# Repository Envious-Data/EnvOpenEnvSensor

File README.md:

# EnvOpenEnvSensor
 a simple sensor pcb with a display to show some environment conditions

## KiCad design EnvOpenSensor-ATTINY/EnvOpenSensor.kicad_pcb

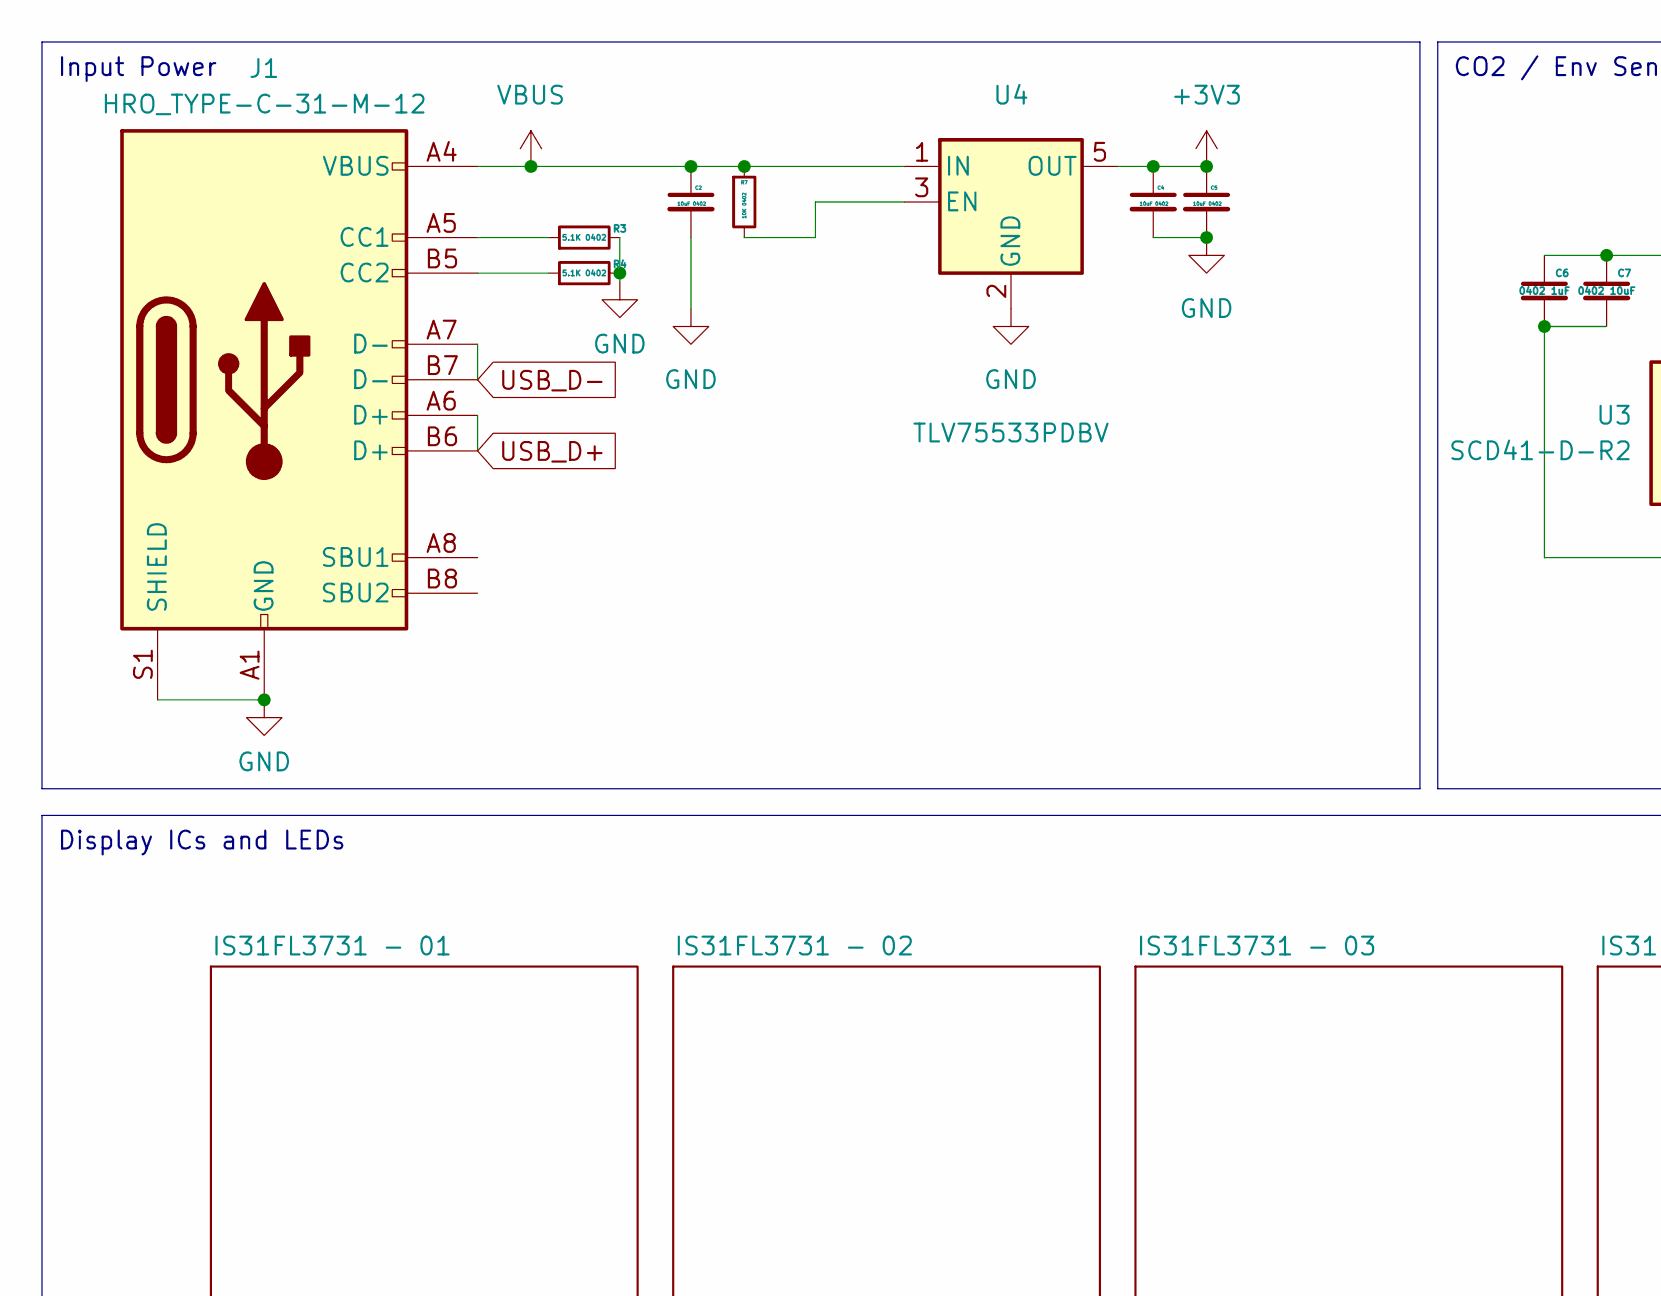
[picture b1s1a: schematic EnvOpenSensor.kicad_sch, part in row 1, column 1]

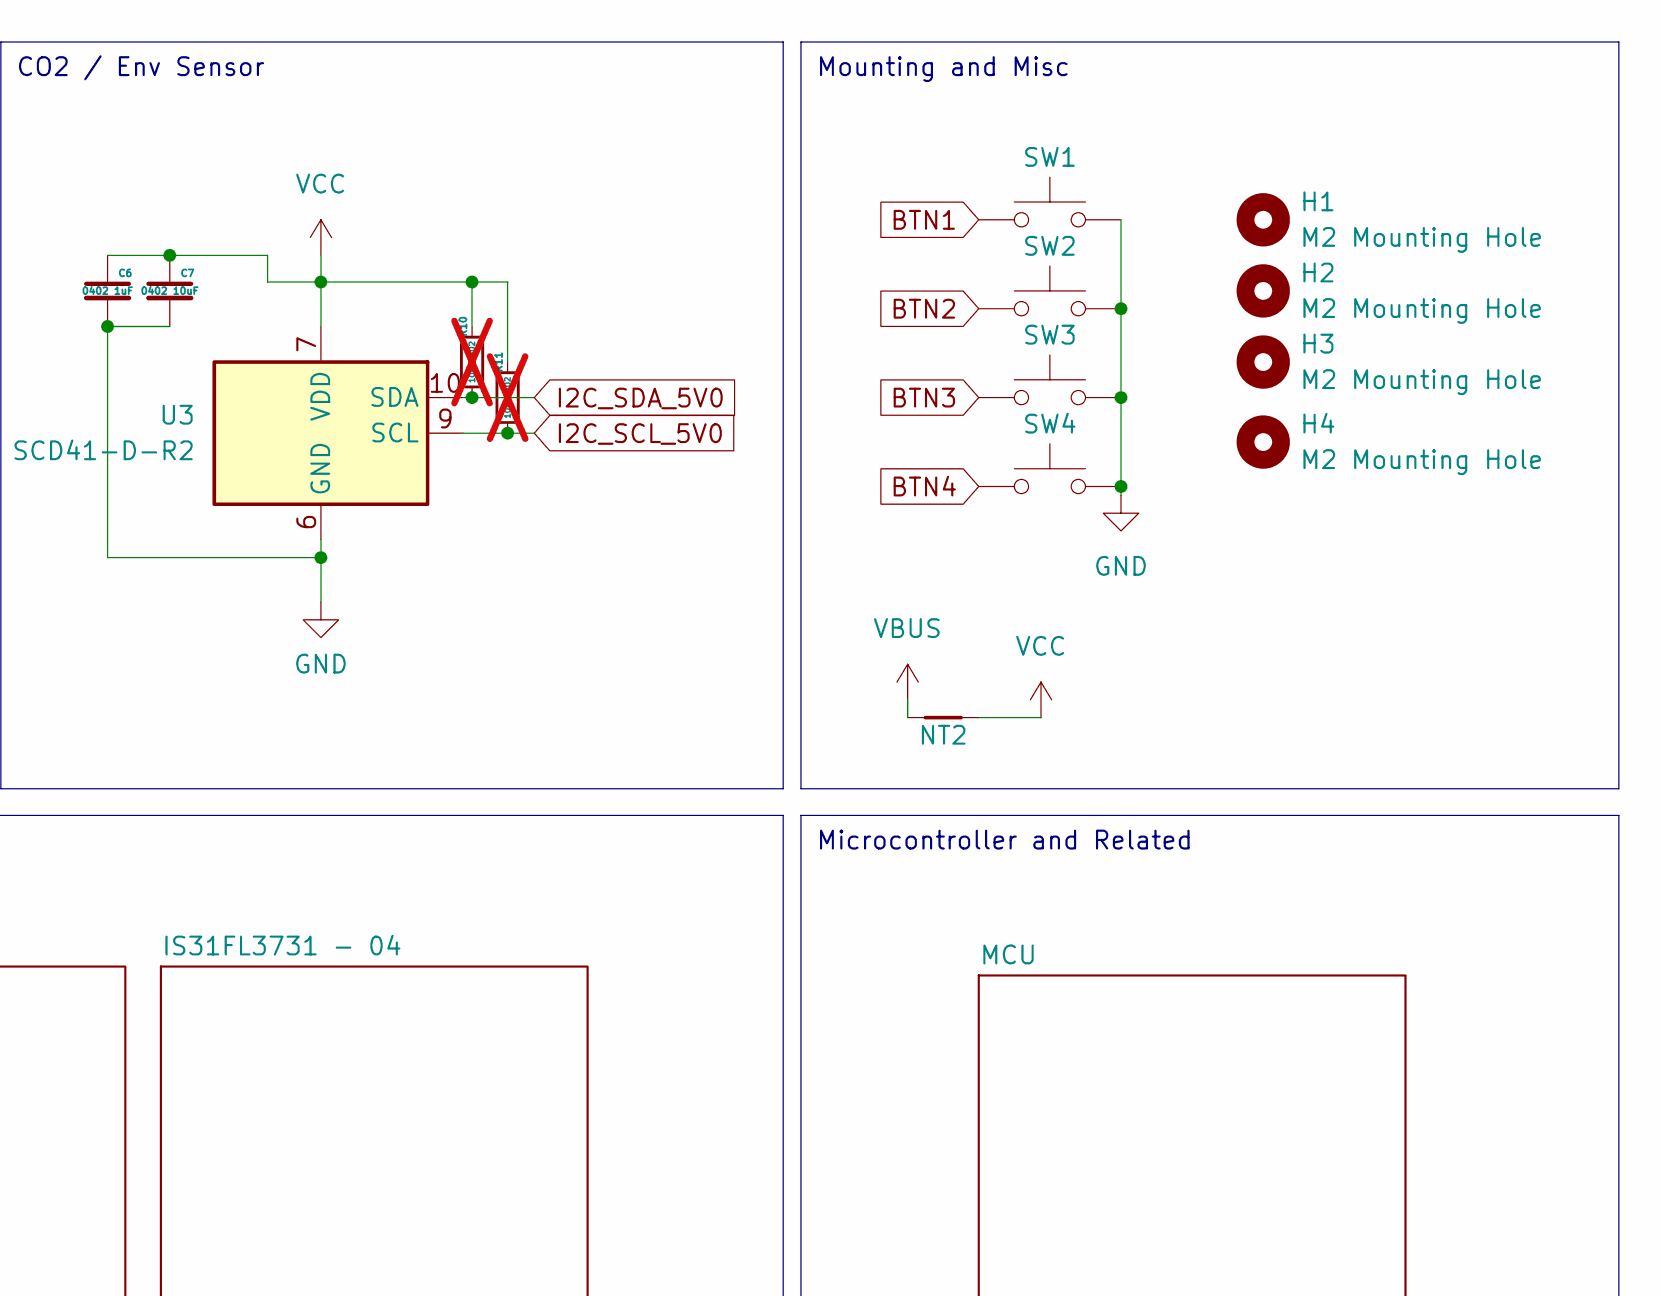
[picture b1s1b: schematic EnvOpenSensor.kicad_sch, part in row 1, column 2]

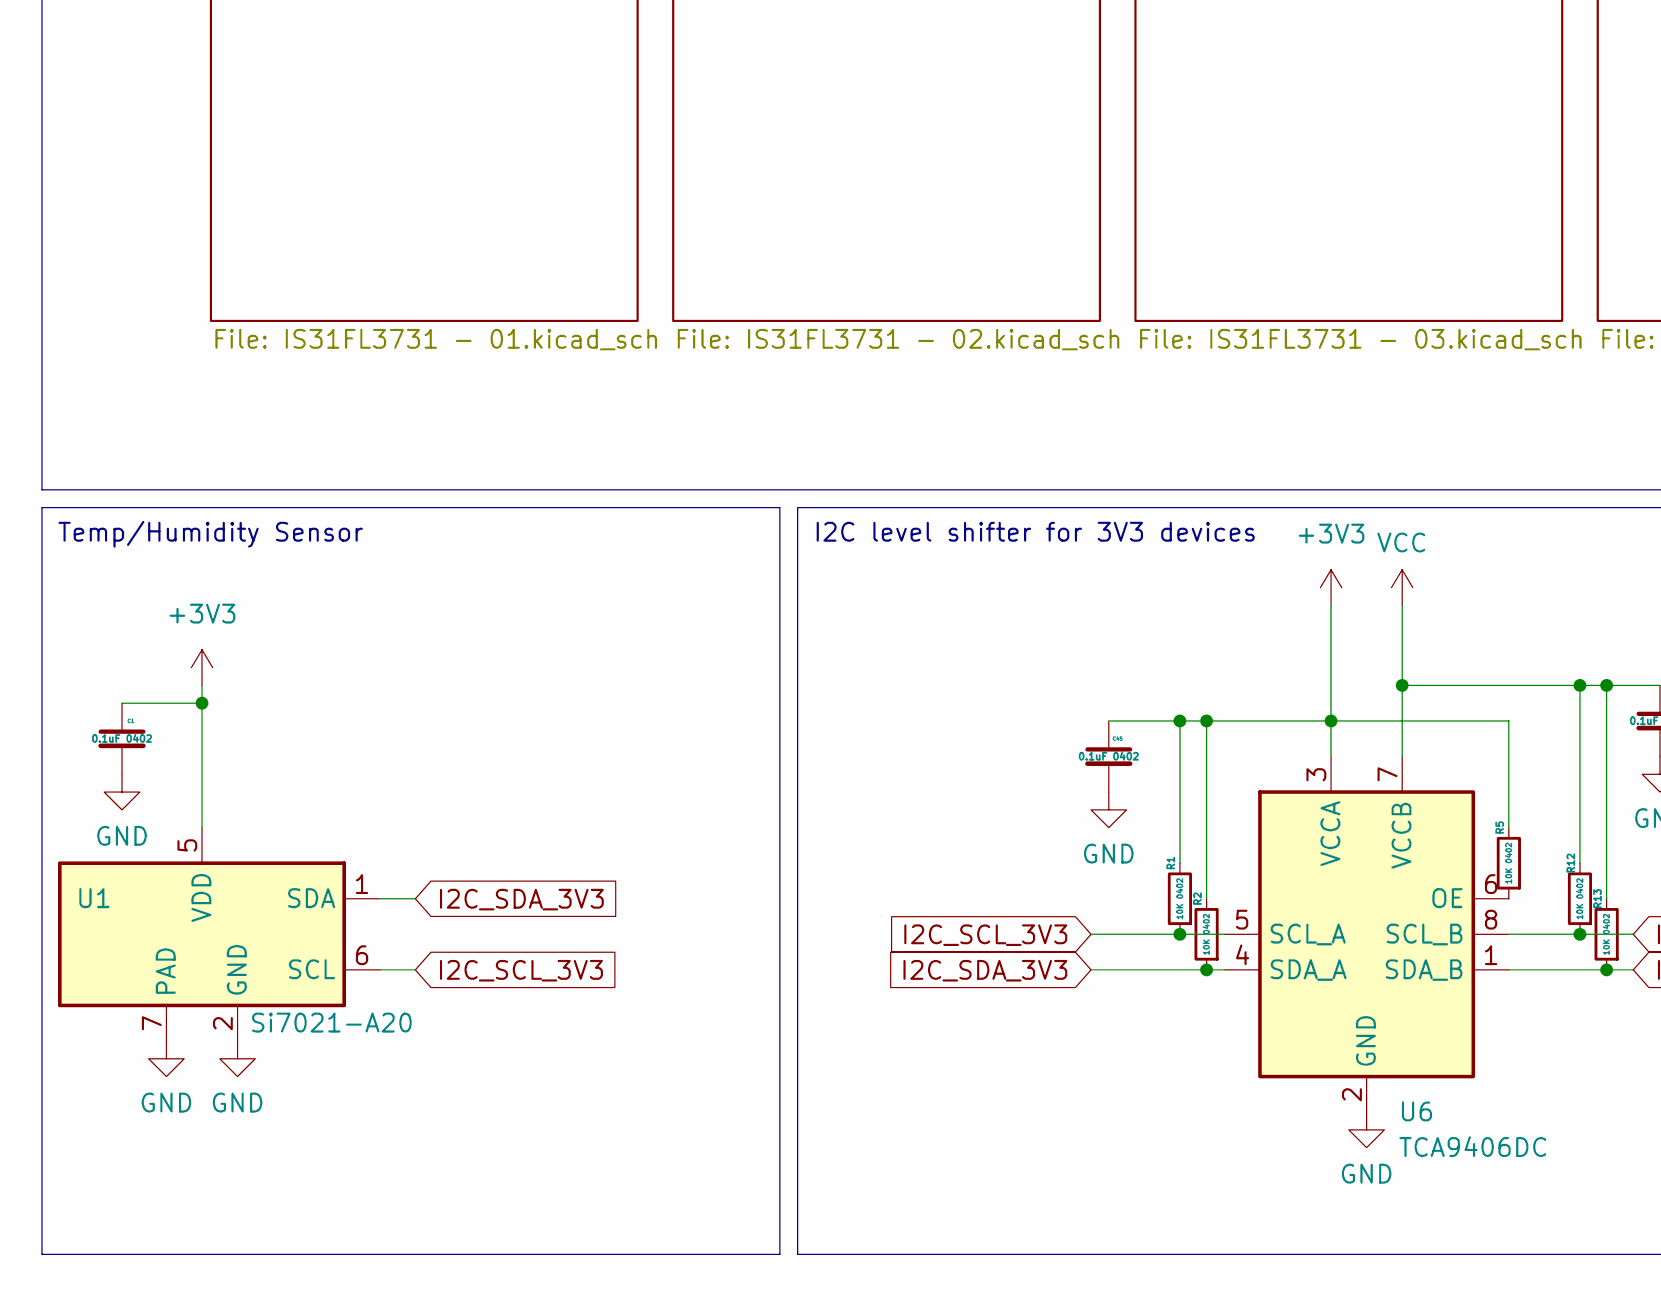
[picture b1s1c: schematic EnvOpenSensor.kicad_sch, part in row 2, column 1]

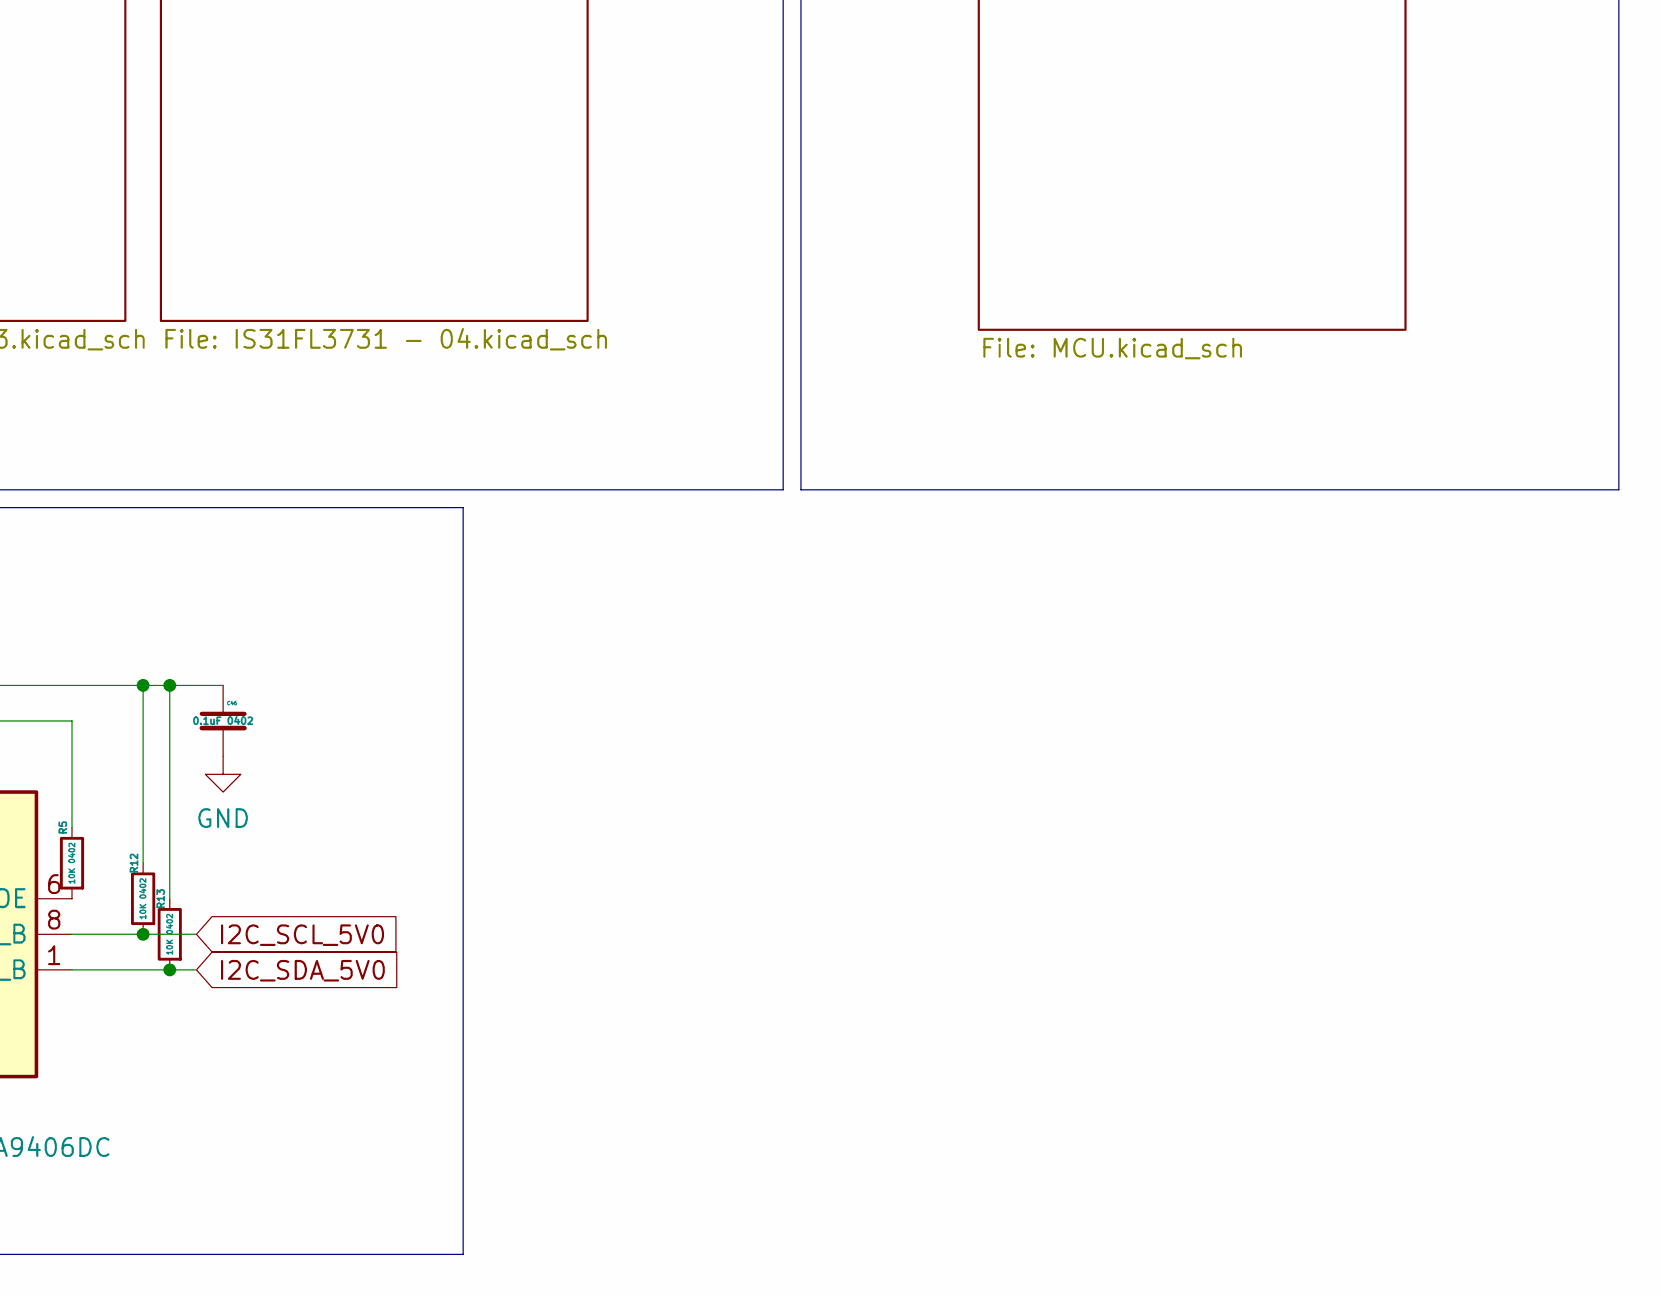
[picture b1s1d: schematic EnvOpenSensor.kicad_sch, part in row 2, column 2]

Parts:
C1, C45, C46: 0.1uF 0402; C_0402_1005Metric
C2, C4, C5: 10uF 0402; C_0402_1005Metric
C6: 0402 1uF; C_0402_1005Metric
C7: 0402 10uF; C_0402_1005Metric
H1, H2, H3, H4: M2 Mounting Hole; MountingHole_2.2mm_M2
J1: HRO_TYPE-C-31-M-12; USB_C_Receptacle_HRO_TYPE-C-31-M-12
NT2: NetTie_2; NetTie-2_THT_Pad1.0mm
R1, R2, R5, R7, R12, R13: 10K 0402; R_0402_1005Metric
R3, R4: 5.1K 0402; R_0402_1005Metric
R10, R11: 10K 0402; R_0402_1005Metric; not fitted
SW1, SW2, SW3, SW4: SW_Push; SW_Cherry_MX_1.00u_PCB
U1: Si7021-A20; DFN-6-1EP_3x3mm_P1mm_EP1.5x2.4mm
U3: SCD41-D-R2; Sensirion_SCD4x-1EP_10.1x10.1mm_P1.25mm_EP4.8x4.8mm
U4: TLV75533PDBV; SOT-23-5
U6: TCA9406DC; VSSOP-8_2.3x2mm_P0.5mm

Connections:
+3V3: C1.1, C4.1, C5.1, C45.1, R1.2, R2.2, R5.2, U1.5 (VDD), U4.5 (OUT), U6.3 (VCCA); also elsewhere on the board
BTN1: SW1.1; also elsewhere on the board
BTN2: SW2.1; also elsewhere on the board
BTN3: SW3.1; also elsewhere on the board
BTN4: SW4.1; also elsewhere on the board
GND: C1.2, C2.2, C4.2, C5.2, C6.2, C7.2, C45.2, C46.2, J1.A1 (GND), J1.A12 (GND), J1.B1 (GND), J1.B12 (GND), J1.S1 (SHIELD), R3.2, R4.2, SW1.2, SW2.2, SW3.2, SW4.2, U1.2 (GND), U1.7 (PAD), U3.6 (GND), U3.20 (GND), U3.21 (GND), U4.2 (GND), U6.2 (GND); also elsewhere on the board
I2C_SCL_3V3: R1.1, U1.6 (SCL), U6.5 (SCL_A); also elsewhere on the board
I2C_SCL_5V0: R11.1, R12.1, U3.9 (SCL), U6.8 (SCL_B); also elsewhere on the board
I2C_SDA_3V3: R2.1, U1.1 (SDA), U6.4 (SDA_A); also elsewhere on the board
I2C_SDA_5V0: R10.1, R13.1, U3.10 (SDA), U6.1 (SDA_B); also elsewhere on the board
unnamed: J1.A5 (CC1), R3.1
unnamed: J1.B5 (CC2), R4.1
unnamed: R7.2, U4.3 (EN)
unnamed: R5.1, U6.6 (OE)
USB_D+: J1.A6 (D+), J1.B6 (D+)
USB_D-: J1.A7 (D-), J1.B7 (D-)
VBUS: C2.1, J1.A4 (VBUS), J1.A9 (VBUS), J1.B4 (VBUS), J1.B9 (VBUS), NT2.1, R7.1, U4.1 (IN)
VCC: C6.1, C7.1, C46.1, NT2.2, R10.2, R11.2, R12.2, R13.2, U3.7 (VDD), U3.19 (VDD), U6.7 (VCCB); also elsewhere on the board

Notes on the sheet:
CO2 / Env Sensor
Temp/Humidity Sensor
Mounting and Misc
I2C level shifter for 3V3 devices
Input Power
Microcontroller and Related
Display ICs and LEDs

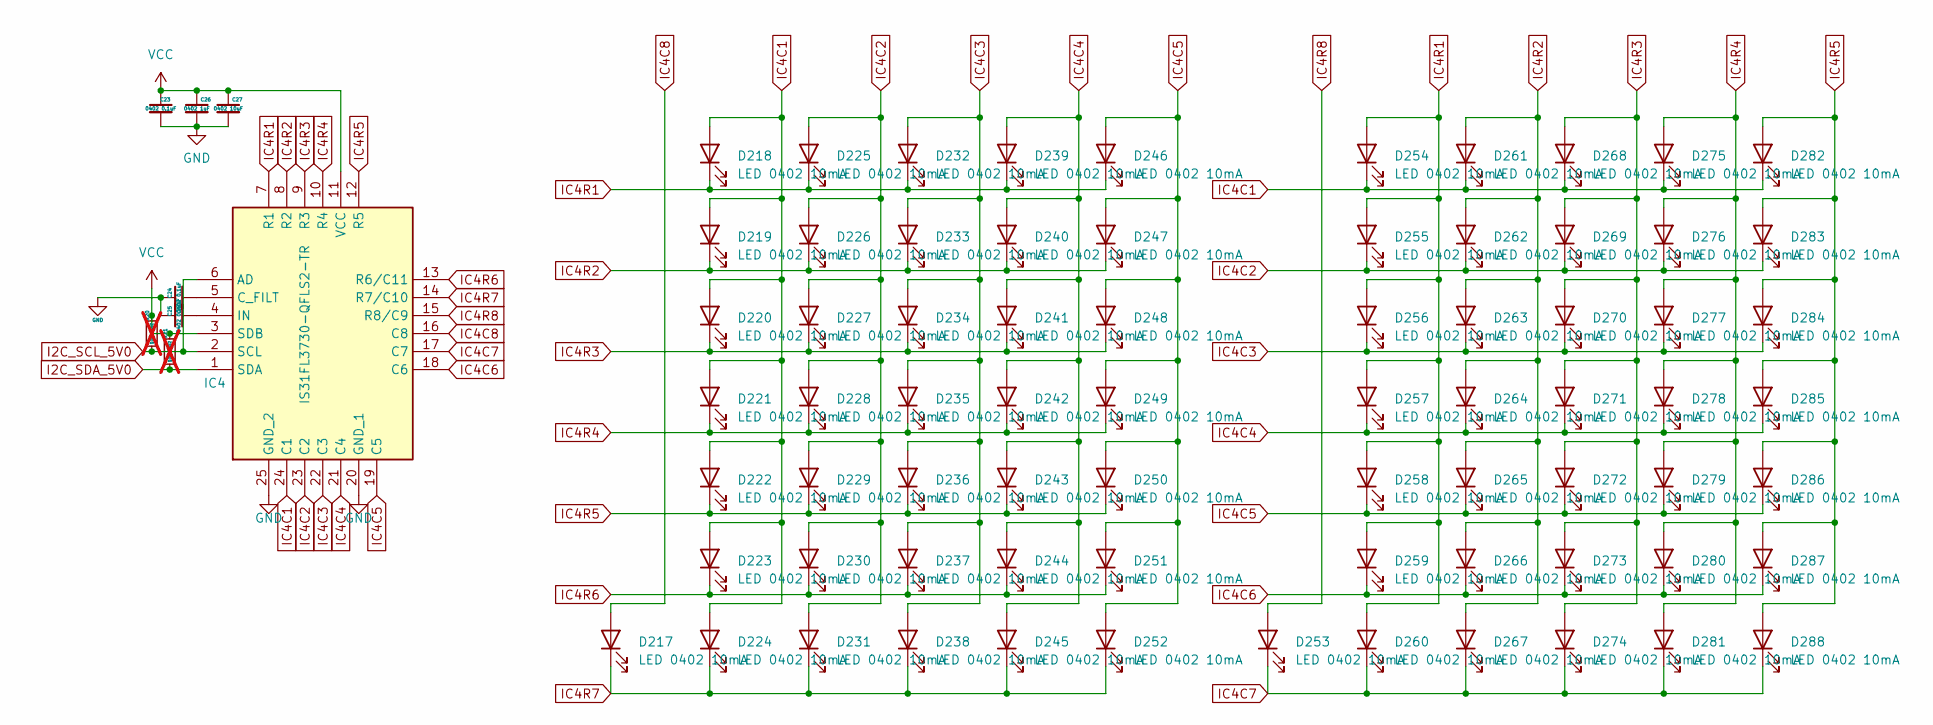
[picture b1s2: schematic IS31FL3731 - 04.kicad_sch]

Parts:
C23, C24: 0402 0.1uF; C_0402_1005Metric
C25: 0402 0.22uF; C_0402_1005Metric
C26: 0402 1uF; C_0402_1005Metric
C27: 0402 10uF; C_0402_1005Metric
D217, D218, D219, D220, D221, D222, D223, D224, D225, D226, D227, D228, D229, D230, D231, D232, D233, D234, D235, D236, D237, D238, D239, D240, D241, D242, D243, D244, D245, D246, D247, D248, D249, D250, D251, D252, D253, D254, D255, D256, D257, D258, D259, D260, D261, D262, D263, D264, D265, D266, D267, D268, D269, D270, D271, D272, D273, D274, D275, D276, D277, D278, D279, D280, D281, D282, D283, D284, D285, D286, D287, D288: LED 0402 10mA; LED_0402_1005Metric
IC4: IS31FL3730-QFLS2-TR; QFN-24-1EP_4x4mm_P0.5mm_EP2.6x2.6mm_ThermalVias; Mouser Part Number 870-IS31FL3730QFLS2R
R20, R21: 10K 0402; R_0402_1005Metric; not fitted

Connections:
GND: C23.2, C24.1, C25.1, C26.2, C27.2, IC4.20 (GND_1), IC4.25 (GND_2); also elsewhere on the board
I2C_SCL_5V0: IC4.2 (SCL), IC4.6 (AD), R20.1; also elsewhere on the board
I2C_SDA_5V0: IC4.1 (SDA), R21.1; also elsewhere on the board
IC4C1: D218.2 (A), D219.2 (A), D220.2 (A), D221.2 (A), D222.2 (A), D223.2 (A), D224.2 (A), D254.1 (K), D261.1 (K), D268.1 (K), D275.1 (K), D282.1 (K), IC4.24 (C1)
IC4C2: D225.2 (A), D226.2 (A), D227.2 (A), D228.2 (A), D229.2 (A), D230.2 (A), D231.2 (A), D255.1 (K), D262.1 (K), D269.1 (K), D276.1 (K), D283.1 (K), IC4.23 (C2)
IC4C3: D232.2 (A), D233.2 (A), D234.2 (A), D235.2 (A), D236.2 (A), D237.2 (A), D238.2 (A), D256.1 (K), D263.1 (K), D270.1 (K), D277.1 (K), D284.1 (K), IC4.22 (C3)
IC4C4: D239.2 (A), D240.2 (A), D241.2 (A), D242.2 (A), D243.2 (A), D244.2 (A), D245.2 (A), D257.1 (K), D264.1 (K), D271.1 (K), D278.1 (K), D285.1 (K), IC4.21 (C4)
IC4C5: D246.2 (A), D247.2 (A), D248.2 (A), D249.2 (A), D250.2 (A), D251.2 (A), D252.2 (A), D258.1 (K), D265.1 (K), D272.1 (K), D279.1 (K), D286.1 (K), IC4.19 (C5)
IC4C6: D259.1 (K), D266.1 (K), D273.1 (K), D280.1 (K), D287.1 (K), IC4.18 (C6)
IC4C7: D253.1 (K), D260.1 (K), D267.1 (K), D274.1 (K), D281.1 (K), D288.1 (K), IC4.17 (C7)
IC4C8: D217.2 (A), IC4.16 (C8)
IC4R1: D218.1 (K), D225.1 (K), D232.1 (K), D239.1 (K), D246.1 (K), D254.2 (A), D255.2 (A), D256.2 (A), D257.2 (A), D258.2 (A), D259.2 (A), D260.2 (A), IC4.7 (R1)
IC4R2: D219.1 (K), D226.1 (K), D233.1 (K), D240.1 (K), D247.1 (K), D261.2 (A), D262.2 (A), D263.2 (A), D264.2 (A), D265.2 (A), D266.2 (A), D267.2 (A), IC4.8 (R2)
IC4R3: D220.1 (K), D227.1 (K), D234.1 (K), D241.1 (K), D248.1 (K), D268.2 (A), D269.2 (A), D270.2 (A), D271.2 (A), D272.2 (A), D273.2 (A), D274.2 (A), IC4.9 (R3)
IC4R4: D221.1 (K), D228.1 (K), D235.1 (K), D242.1 (K), D249.1 (K), D275.2 (A), D276.2 (A), D277.2 (A), D278.2 (A), D279.2 (A), D280.2 (A), D281.2 (A), IC4.10 (R4)
IC4R5: D222.1 (K), D229.1 (K), D236.1 (K), D243.1 (K), D250.1 (K), D282.2 (A), D283.2 (A), D284.2 (A), D285.2 (A), D286.2 (A), D287.2 (A), D288.2 (A), IC4.12 (R5)
IC4R6: D223.1 (K), D230.1 (K), D237.1 (K), D244.1 (K), D251.1 (K), IC4.13 (R6/C11)
IC4R7: D217.1 (K), D224.1 (K), D231.1 (K), D238.1 (K), D245.1 (K), D252.1 (K), IC4.14 (R7/C10)
IC4R8: D253.2 (A), IC4.15 (R8/C9)
unnamed: C24.2, IC4.5 (C_FILT)
unnamed: C25.2, IC4.4 (IN)
VCC: C23.1, C26.1, C27.1, IC4.3 (SDB), IC4.11 (VCC), R20.2, R21.2; also elsewhere on the board

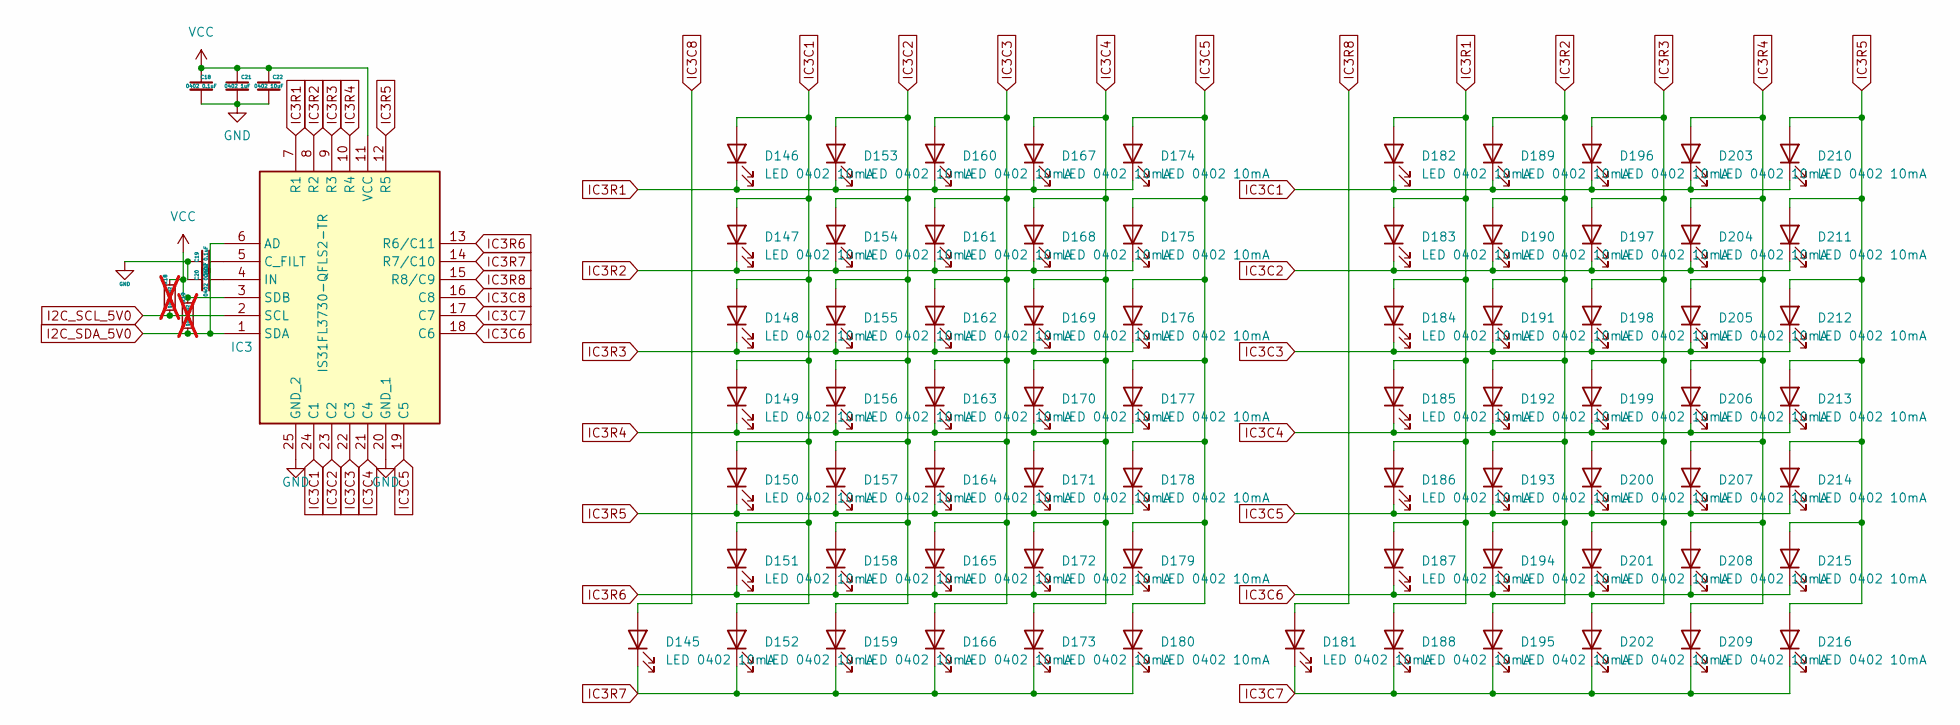
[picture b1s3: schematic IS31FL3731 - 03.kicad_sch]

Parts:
C18, C19: 0402 0.1uF; C_0402_1005Metric
C20: 0402 0.22uF; C_0402_1005Metric
C21: 0402 1uF; C_0402_1005Metric
C22: 0402 10uF; C_0402_1005Metric
D145, D146, D147, D148, D149, D150, D151, D152, D153, D154, D155, D156, D157, D158, D159, D160, D161, D162, D163, D164, D165, D166, D167, D168, D169, D170, D171, D172, D173, D174, D175, D176, D177, D178, D179, D180, D181, D182, D183, D184, D185, D186, D187, D188, D189, D190, D191, D192, D193, D194, D195, D196, D197, D198, D199, D200, D201, D202, D203, D204, D205, D206, D207, D208, D209, D210, D211, D212, D213, D214, D215, D216: LED 0402 10mA; LED_0402_1005Metric
IC3: IS31FL3730-QFLS2-TR; QFN-24-1EP_4x4mm_P0.5mm_EP2.6x2.6mm_ThermalVias; Mouser Part Number 870-IS31FL3730QFLS2R
R18, R19: 10K 0402; R_0402_1005Metric; not fitted

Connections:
GND: C18.2, C19.1, C20.1, C21.2, C22.2, IC3.20 (GND_1), IC3.25 (GND_2); also elsewhere on the board
I2C_SCL_5V0: IC3.2 (SCL), R18.1; also elsewhere on the board
I2C_SDA_5V0: IC3.1 (SDA), IC3.6 (AD), R19.1; also elsewhere on the board
IC3C1: D146.2 (A), D147.2 (A), D148.2 (A), D149.2 (A), D150.2 (A), D151.2 (A), D152.2 (A), D182.1 (K), D189.1 (K), D196.1 (K), D203.1 (K), D210.1 (K), IC3.24 (C1)
IC3C2: D153.2 (A), D154.2 (A), D155.2 (A), D156.2 (A), D157.2 (A), D158.2 (A), D159.2 (A), D183.1 (K), D190.1 (K), D197.1 (K), D204.1 (K), D211.1 (K), IC3.23 (C2)
IC3C3: D160.2 (A), D161.2 (A), D162.2 (A), D163.2 (A), D164.2 (A), D165.2 (A), D166.2 (A), D184.1 (K), D191.1 (K), D198.1 (K), D205.1 (K), D212.1 (K), IC3.22 (C3)
IC3C4: D167.2 (A), D168.2 (A), D169.2 (A), D170.2 (A), D171.2 (A), D172.2 (A), D173.2 (A), D185.1 (K), D192.1 (K), D199.1 (K), D206.1 (K), D213.1 (K), IC3.21 (C4)
IC3C5: D174.2 (A), D175.2 (A), D176.2 (A), D177.2 (A), D178.2 (A), D179.2 (A), D180.2 (A), D186.1 (K), D193.1 (K), D200.1 (K), D207.1 (K), D214.1 (K), IC3.19 (C5)
IC3C6: D187.1 (K), D194.1 (K), D201.1 (K), D208.1 (K), D215.1 (K), IC3.18 (C6)
IC3C7: D181.1 (K), D188.1 (K), D195.1 (K), D202.1 (K), D209.1 (K), D216.1 (K), IC3.17 (C7)
IC3C8: D145.2 (A), IC3.16 (C8)
IC3R1: D146.1 (K), D153.1 (K), D160.1 (K), D167.1 (K), D174.1 (K), D182.2 (A), D183.2 (A), D184.2 (A), D185.2 (A), D186.2 (A), D187.2 (A), D188.2 (A), IC3.7 (R1)
IC3R2: D147.1 (K), D154.1 (K), D161.1 (K), D168.1 (K), D175.1 (K), D189.2 (A), D190.2 (A), D191.2 (A), D192.2 (A), D193.2 (A), D194.2 (A), D195.2 (A), IC3.8 (R2)
IC3R3: D148.1 (K), D155.1 (K), D162.1 (K), D169.1 (K), D176.1 (K), D196.2 (A), D197.2 (A), D198.2 (A), D199.2 (A), D200.2 (A), D201.2 (A), D202.2 (A), IC3.9 (R3)
IC3R4: D149.1 (K), D156.1 (K), D163.1 (K), D170.1 (K), D177.1 (K), D203.2 (A), D204.2 (A), D205.2 (A), D206.2 (A), D207.2 (A), D208.2 (A), D209.2 (A), IC3.10 (R4)
IC3R5: D150.1 (K), D157.1 (K), D164.1 (K), D171.1 (K), D178.1 (K), D210.2 (A), D211.2 (A), D212.2 (A), D213.2 (A), D214.2 (A), D215.2 (A), D216.2 (A), IC3.12 (R5)
IC3R6: D151.1 (K), D158.1 (K), D165.1 (K), D172.1 (K), D179.1 (K), IC3.13 (R6/C11)
IC3R7: D145.1 (K), D152.1 (K), D159.1 (K), D166.1 (K), D173.1 (K), D180.1 (K), IC3.14 (R7/C10)
IC3R8: D181.2 (A), IC3.15 (R8/C9)
unnamed: C19.2, IC3.5 (C_FILT)
unnamed: C20.2, IC3.4 (IN)
VCC: C18.1, C21.1, C22.1, IC3.3 (SDB), IC3.11 (VCC), R18.2, R19.2; also elsewhere on the board

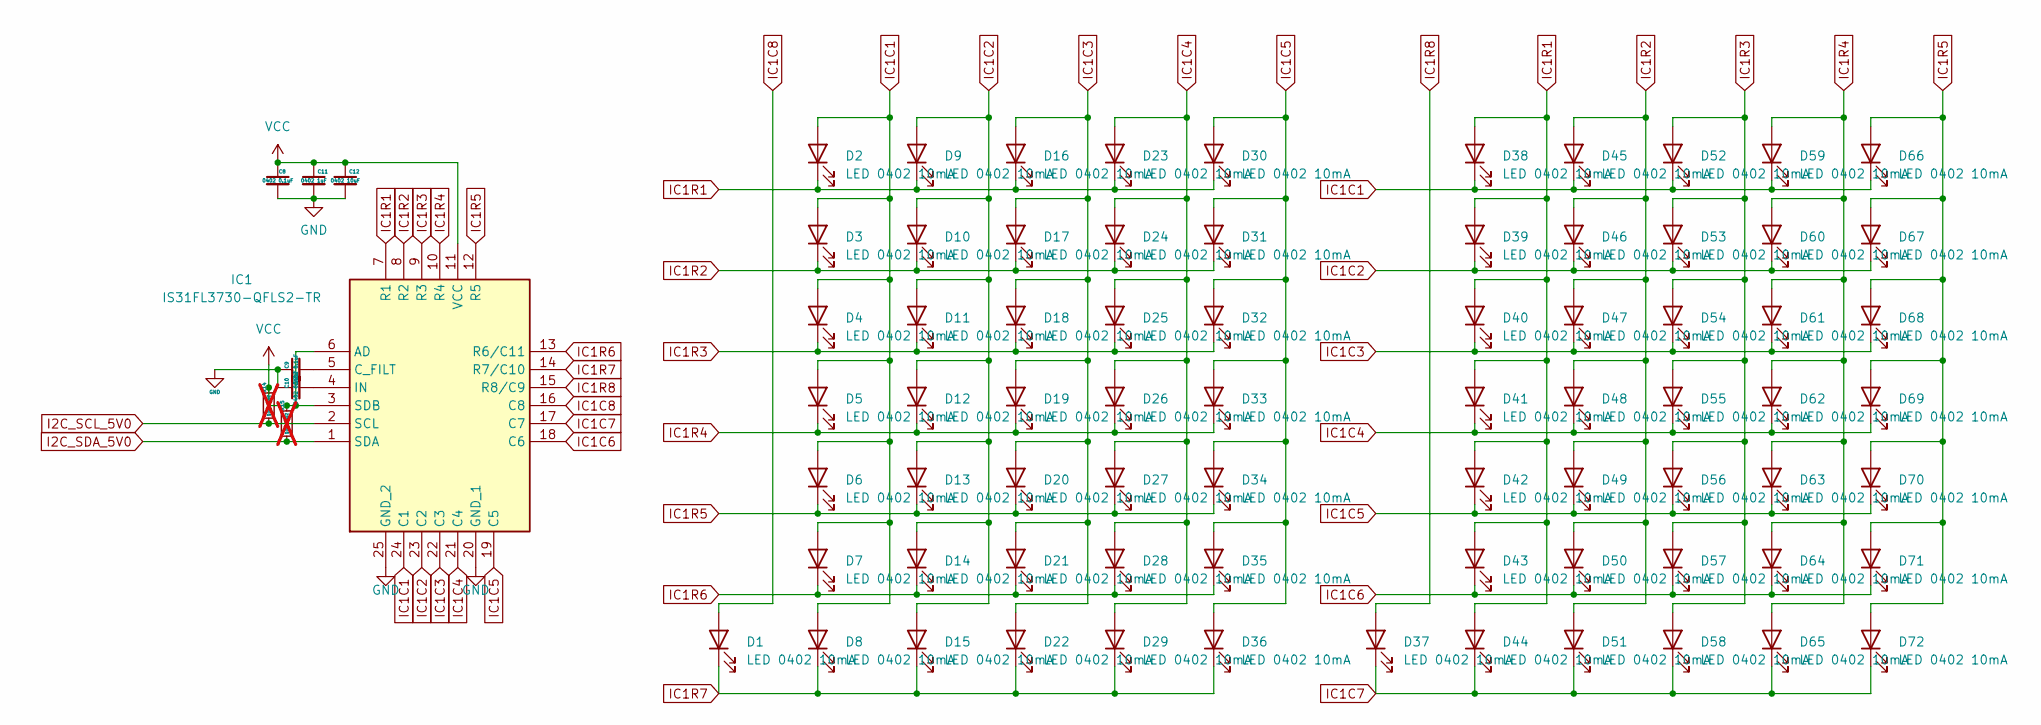
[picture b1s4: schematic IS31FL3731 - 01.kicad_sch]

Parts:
C8, C9: 0402 0.1uF; C_0402_1005Metric
C10: 0402 0.22uF; C_0402_1005Metric
C11: 0402 1uF; C_0402_1005Metric
C12: 0402 10uF; C_0402_1005Metric
D1, D2, D3, D4, D5, D6, D7, D8, D9, D10, D11, D12, D13, D14, D15, D16, D17, D18, D19, D20, D21, D22, D23, D24, D25, D26, D27, D28, D29, D30, D31, D32, D33, D34, D35, D36, D37, D38, D39, D40, D41, D42, D43, D44, D45, D46, D47, D48, D49, D50, D51, D52, D53, D54, D55, D56, D57, D58, D59, D60, D61, D62, D63, D64, D65, D66, D67, D68, D69, D70, D71, D72: LED 0402 10mA; LED_0402_1005Metric
IC1: IS31FL3730-QFLS2-TR; QFN-24-1EP_4x4mm_P0.5mm_EP2.6x2.6mm_ThermalVias; Mouser Part Number 870-IS31FL3730QFLS2R
R14, R15: 10K 0402; R_0402_1005Metric; not fitted

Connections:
GND: C8.2, C9.1, C10.1, C11.2, C12.2, IC1.20 (GND_1), IC1.25 (GND_2); also elsewhere on the board
I2C_SCL_5V0: IC1.2 (SCL), R14.1; also elsewhere on the board
I2C_SDA_5V0: IC1.1 (SDA), R15.1; also elsewhere on the board
IC1C1: D2.2 (A), D3.2 (A), D4.2 (A), D5.2 (A), D6.2 (A), D7.2 (A), D8.2 (A), D38.1 (K), D45.1 (K), D52.1 (K), D59.1 (K), D66.1 (K), IC1.24 (C1)
IC1C2: D9.2 (A), D10.2 (A), D11.2 (A), D12.2 (A), D13.2 (A), D14.2 (A), D15.2 (A), D39.1 (K), D46.1 (K), D53.1 (K), D60.1 (K), D67.1 (K), IC1.23 (C2)
IC1C3: D16.2 (A), D17.2 (A), D18.2 (A), D19.2 (A), D20.2 (A), D21.2 (A), D22.2 (A), D40.1 (K), D47.1 (K), D54.1 (K), D61.1 (K), D68.1 (K), IC1.22 (C3)
IC1C4: D23.2 (A), D24.2 (A), D25.2 (A), D26.2 (A), D27.2 (A), D28.2 (A), D29.2 (A), D41.1 (K), D48.1 (K), D55.1 (K), D62.1 (K), D69.1 (K), IC1.21 (C4)
IC1C5: D30.2 (A), D31.2 (A), D32.2 (A), D33.2 (A), D34.2 (A), D35.2 (A), D36.2 (A), D42.1 (K), D49.1 (K), D56.1 (K), D63.1 (K), D70.1 (K), IC1.19 (C5)
IC1C6: D43.1 (K), D50.1 (K), D57.1 (K), D64.1 (K), D71.1 (K), IC1.18 (C6)
IC1C7: D37.1 (K), D44.1 (K), D51.1 (K), D58.1 (K), D65.1 (K), D72.1 (K), IC1.17 (C7)
IC1C8: D1.2 (A), IC1.16 (C8)
IC1R1: D2.1 (K), D9.1 (K), D16.1 (K), D23.1 (K), D30.1 (K), D38.2 (A), D39.2 (A), D40.2 (A), D41.2 (A), D42.2 (A), D43.2 (A), D44.2 (A), IC1.7 (R1)
IC1R2: D3.1 (K), D10.1 (K), D17.1 (K), D24.1 (K), D31.1 (K), D45.2 (A), D46.2 (A), D47.2 (A), D48.2 (A), D49.2 (A), D50.2 (A), D51.2 (A), IC1.8 (R2)
IC1R3: D4.1 (K), D11.1 (K), D18.1 (K), D25.1 (K), D32.1 (K), D52.2 (A), D53.2 (A), D54.2 (A), D55.2 (A), D56.2 (A), D57.2 (A), D58.2 (A), IC1.9 (R3)
IC1R4: D5.1 (K), D12.1 (K), D19.1 (K), D26.1 (K), D33.1 (K), D59.2 (A), D60.2 (A), D61.2 (A), D62.2 (A), D63.2 (A), D64.2 (A), D65.2 (A), IC1.10 (R4)
IC1R5: D6.1 (K), D13.1 (K), D20.1 (K), D27.1 (K), D34.1 (K), D66.2 (A), D67.2 (A), D68.2 (A), D69.2 (A), D70.2 (A), D71.2 (A), D72.2 (A), IC1.12 (R5)
IC1R6: D7.1 (K), D14.1 (K), D21.1 (K), D28.1 (K), D35.1 (K), IC1.13 (R6/C11)
IC1R7: D1.1 (K), D8.1 (K), D15.1 (K), D22.1 (K), D29.1 (K), D36.1 (K), IC1.14 (R7/C10)
IC1R8: D37.2 (A), IC1.15 (R8/C9)
unnamed: C9.2, IC1.5 (C_FILT)
unnamed: C10.2, IC1.4 (IN)
VCC: C8.1, C11.1, C12.1, IC1.3 (SDB), IC1.6 (AD), IC1.11 (VCC), R14.2, R15.2; also elsewhere on the board
